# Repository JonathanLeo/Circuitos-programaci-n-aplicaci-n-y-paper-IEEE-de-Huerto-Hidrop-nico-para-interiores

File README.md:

# Circuitos-programaci-n-aplicaci-n-y-paper-IEEE-de-Huerto-Hidrop-nico-para-interiores

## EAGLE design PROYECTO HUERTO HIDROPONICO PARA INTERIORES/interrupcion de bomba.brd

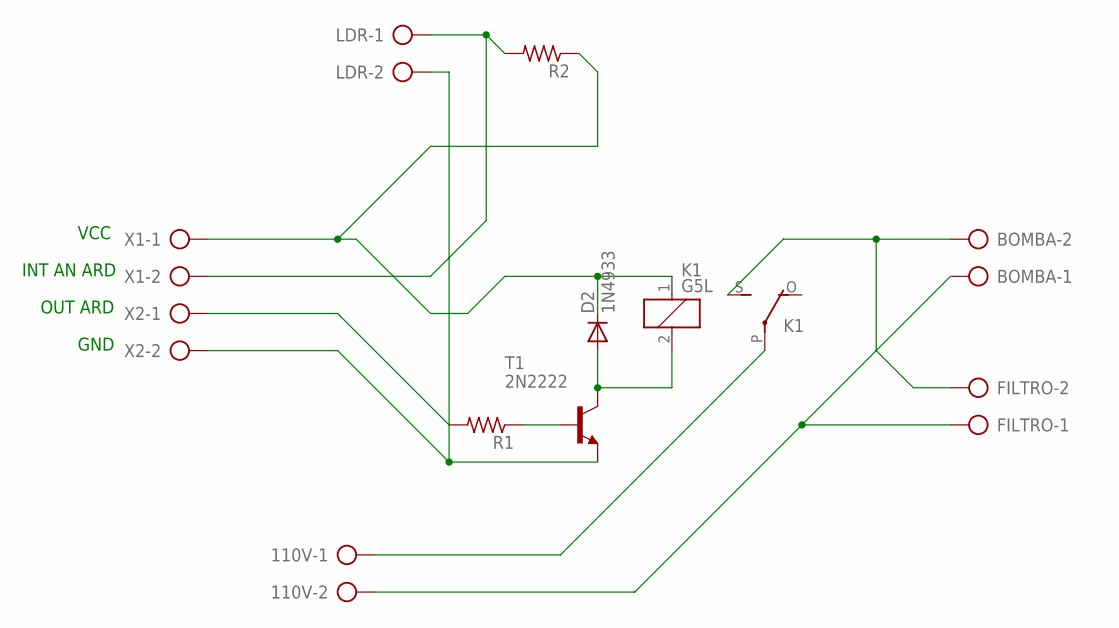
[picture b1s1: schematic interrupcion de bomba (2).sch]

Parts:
110V: AK500/2-H
BOMBA: AK500/2-H
D2: 1N4933; DO41-10
FILTRO: AK500/2-H
K1: G5L; G5LE
LDR: AK500/2-H
R1, R2: R-US_0207/10; 0207/10
T1: 2N2222; TO18
X1, X2: AK500/2-H

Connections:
unnamed: R1.1, T1.2 (B)
unnamed: D2.A, K1.2, T1.3 (C)
unnamed: D2.C, K1.1, R2.1, X1.1
unnamed: 110V.1, K1.P
unnamed: BOMBA.2, FILTRO.2, K1.S
unnamed: R1.2, X2.1
unnamed: 110V.2, BOMBA.1, FILTRO.1
unnamed: LDR.2, T1.1 (E), X2.2
unnamed: LDR.1, R2.2, X1.2

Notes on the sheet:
GND
OUT ARD
INT AN ARD
VCC

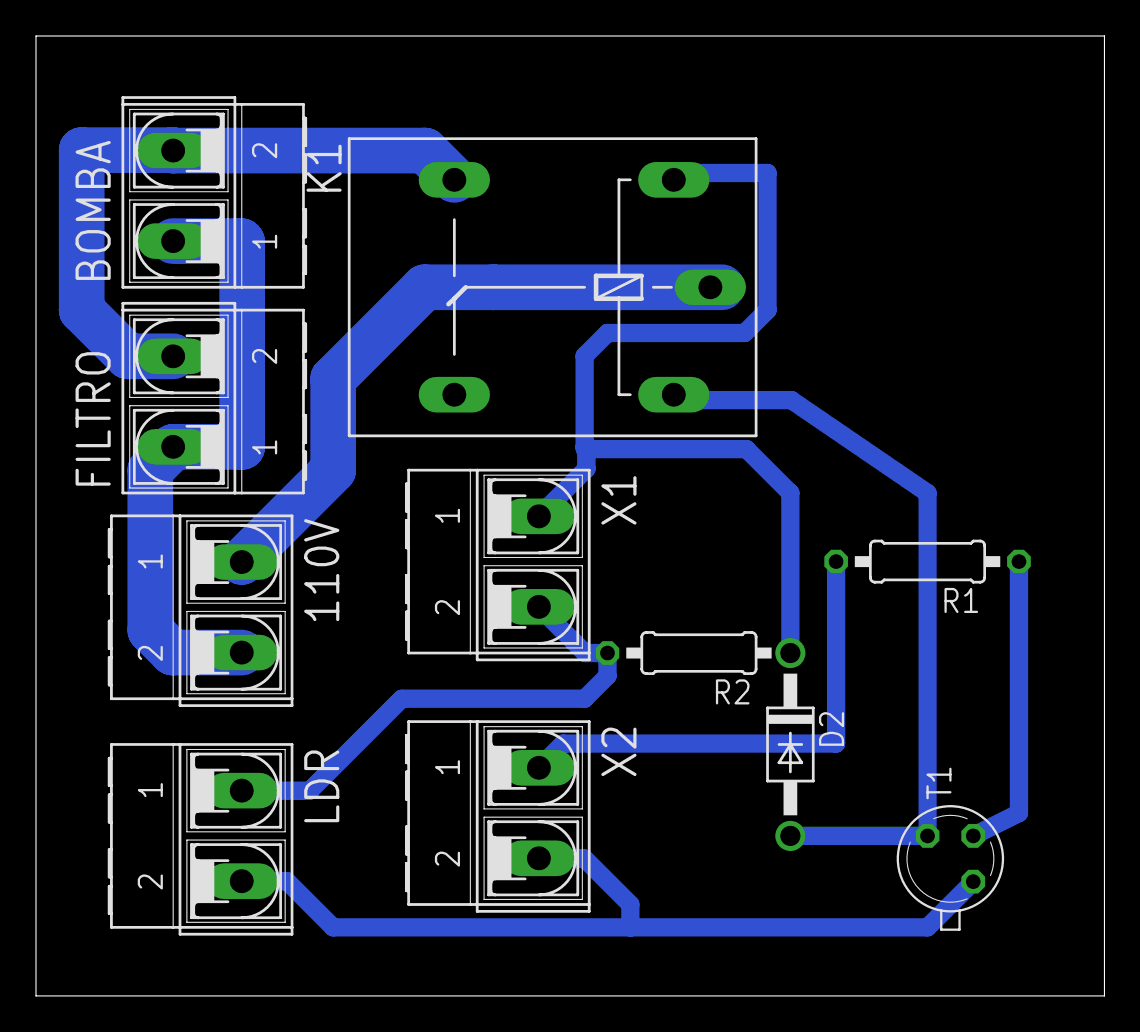
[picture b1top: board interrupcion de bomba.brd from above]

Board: 2 copper layers, 59.4 x 53.3 mm, 11 parts (0 on the bottom side), 9 nets.
